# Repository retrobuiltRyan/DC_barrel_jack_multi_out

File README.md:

# DC_barrel_jack_multi_out
Power splitter for 2.1x5.1mm DC barrel jacks

as seen in this video (near end):
https://youtu.be/6R5AQ15R8a4

example application with a pico ATX psu:

| Reference           | Value                     | Qty | DigiKey P/N      |
|---------------------|---------------------------|-----|------------------|
| D1,D2              | LED                        | 2   | 1080-1419-1-ND   |
| H1,H2,H3,H4        | MountingHole_M3            | 4   |                  |
| J1,J3-J9           | Barrel_Jack                | 8   | EJ508A-ND        |
| J2                 | Screw_Terminal_4_P5.00mm   | 1   | 277-1667-ND      |
| R1,R2              | 5k                         | 2   | 311-100KFRCT-ND  |
| S1,S2              | ~                          | 2   | EG5617-ND        |

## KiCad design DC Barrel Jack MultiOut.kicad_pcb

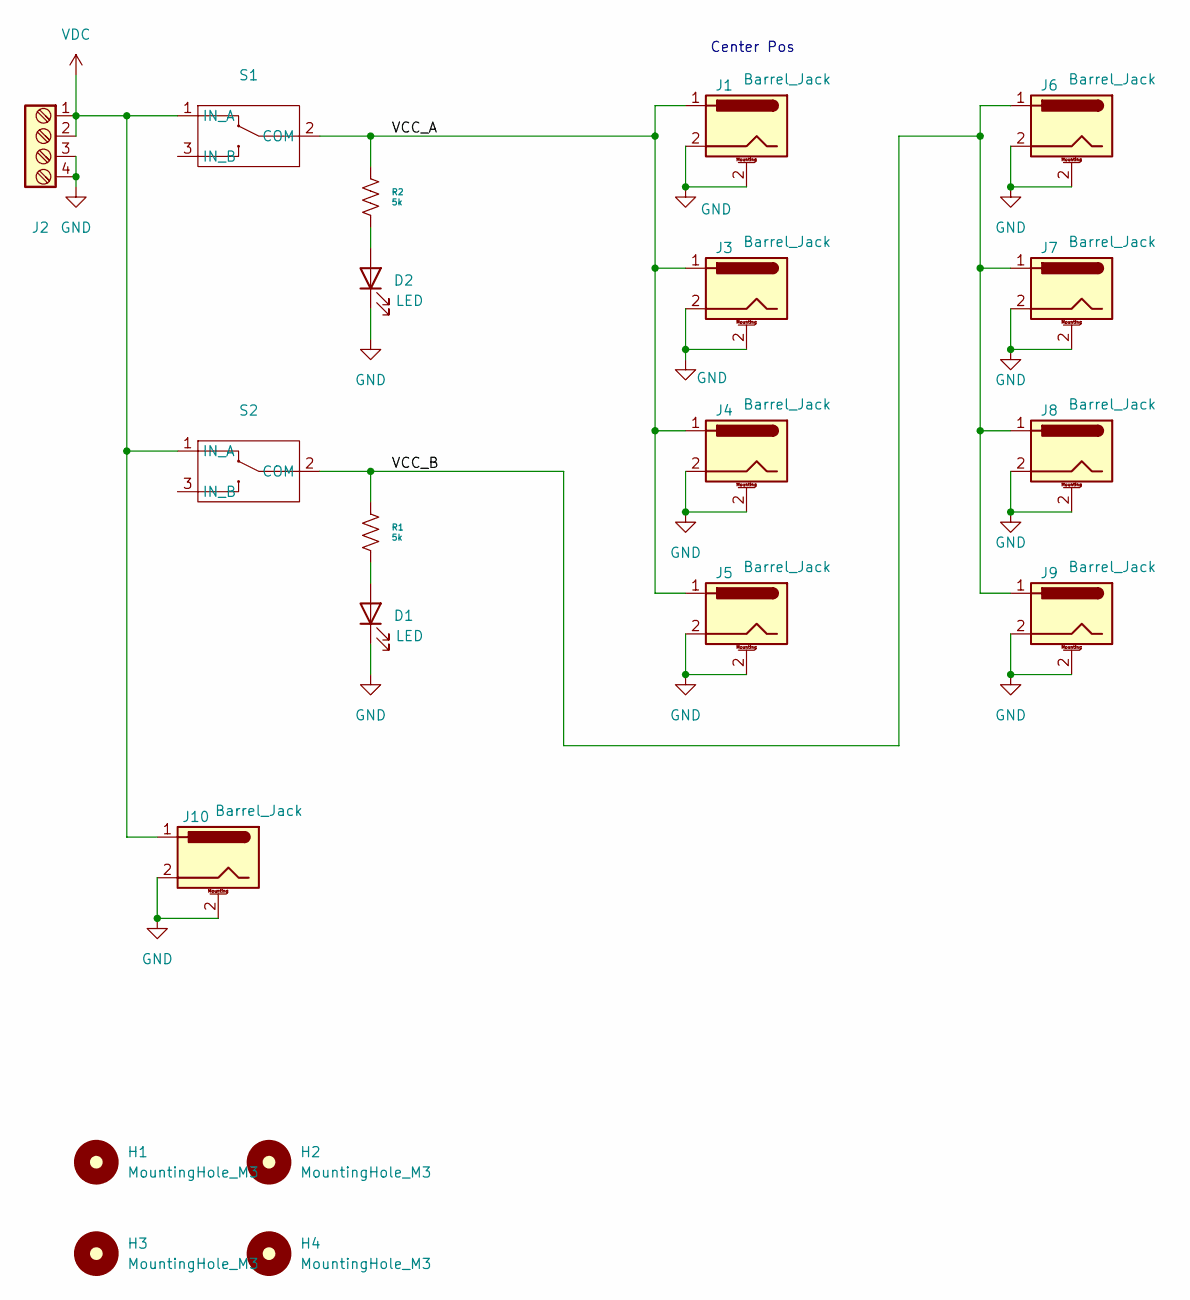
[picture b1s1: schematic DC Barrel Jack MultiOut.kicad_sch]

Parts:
D1, D2: LED; LED_1206_3216Metric
H1, H2, H3, H4: MountingHole_M3; MountingHole_3.2mm_M3
J1, J3, J4, J5, J6, J7, J8, J9, J10: Barrel_Jack; BarrelJack_GCT_DCJ200-10-A_Horizontal; DigiKey P/N EJ508A-ND
J2: Screw_Terminal_4_P5.00mm; TerminalBlock_Phoenix_PT-1,5-4-5.0-H_1x04_P5.00mm_Horizontal; DigiKey P/N 277-1667-ND
R1, R2: 5k; R_1206_3216Metric; DigiKey P/N 311-100KFRCT-ND
S1, S2: SPDT_ Rocker_Switch; DigiKey P/N EG5617-ND

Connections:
/VCC_A: J1.1, J3.1, J4.1, J5.1, R2.1, S1.2 (COM)
/VCC_B: J6.1, J7.1, J8.1, J9.1, R1.1, S2.2 (COM)
GND: D1.1 (K), D2.1 (K), J1.2, J2.3, J2.4, J3.2, J4.2, J5.2, J6.2, J7.2, J8.2, J9.2, J10.2
unnamed: D1.2 (A), R1.2
unnamed: D2.2 (A), R2.2
VDC: J2.1, J2.2, J10.1, S1.1 (IN_A), S2.1 (IN_A)

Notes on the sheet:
Center Pos

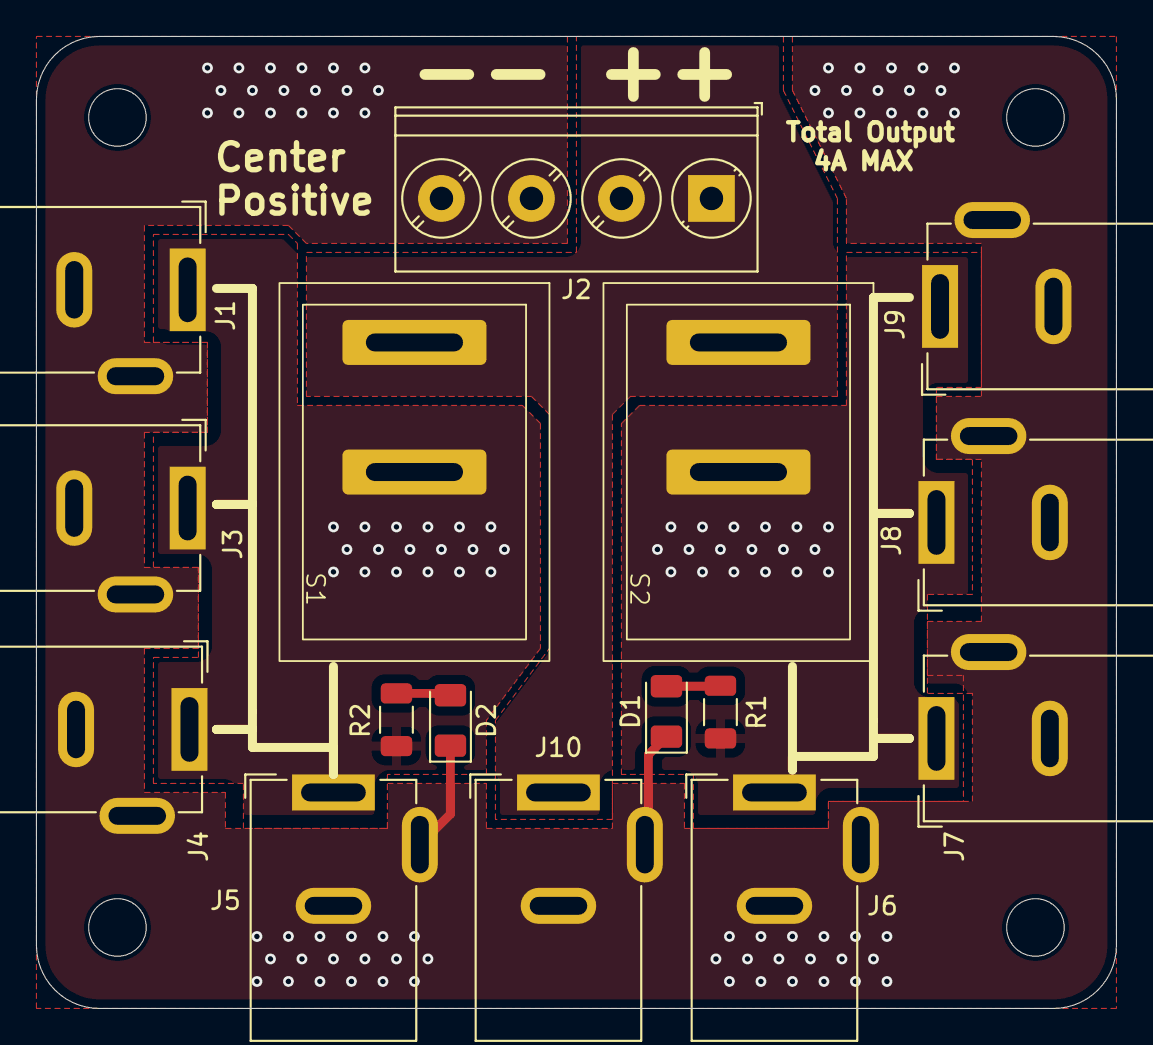
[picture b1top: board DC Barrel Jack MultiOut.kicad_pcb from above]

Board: 2 copper layers, 60.0 x 54.0 mm, 20 parts (0 on the bottom side), 6 nets.

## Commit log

2025-07-13 kiCAD design files

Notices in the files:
DC Barrel Jack MultiOut.kicad_pcb:
(c) 2025 Ryan Bates
